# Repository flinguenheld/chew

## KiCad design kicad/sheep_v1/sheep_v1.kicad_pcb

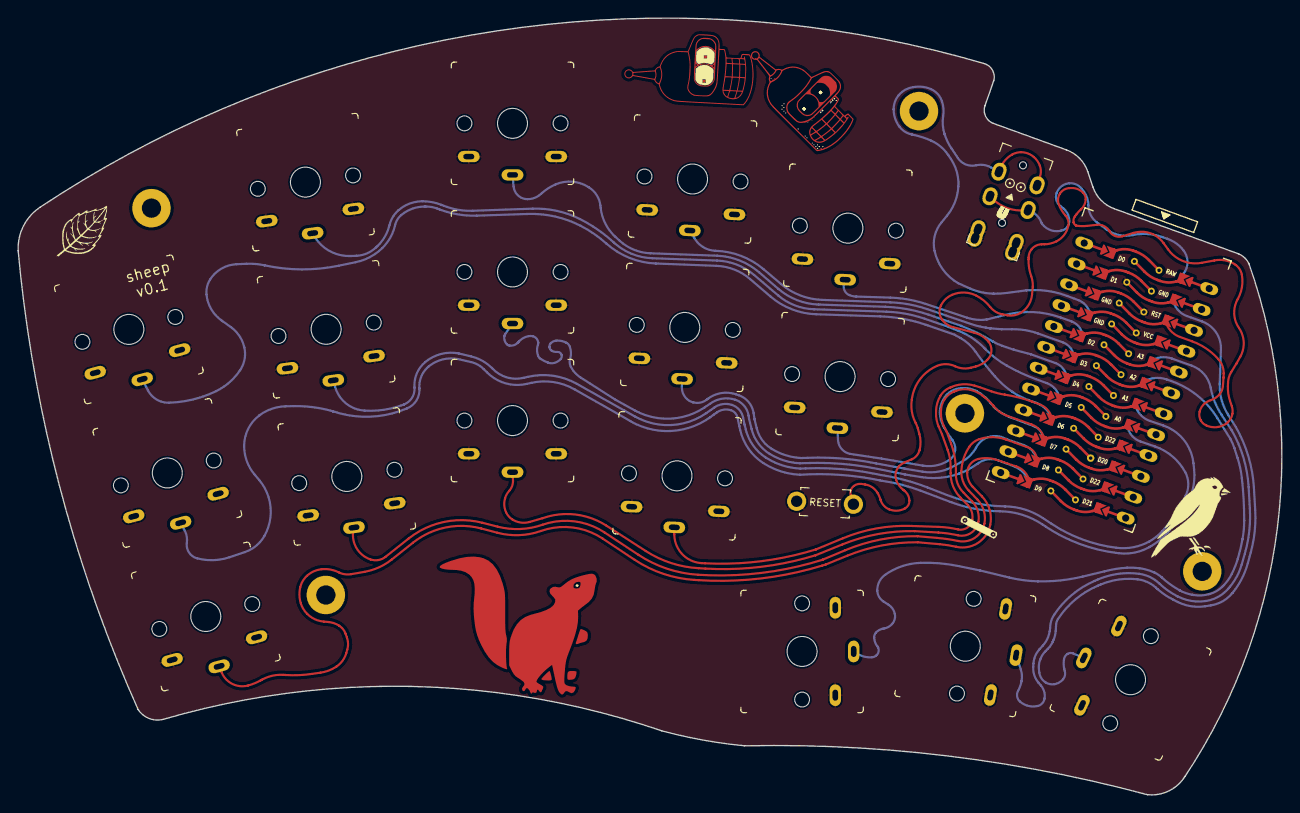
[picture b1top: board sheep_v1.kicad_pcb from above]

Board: 2 copper layers, 144.6 x 88.9 mm, 20 parts (0 on the bottom side), 21 nets.

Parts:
J2: AudioJack4dpb; TRRS-PJ-DPB2
RSW2: SW_PUSH; ResetSW_1side
SW1, SW2, SW3, SW4, SW5, SW6, SW7, SW8, SW9, SW10, SW11, SW12, SW13, SW14, SW15, SW16, SW17: SW_Push; SW_PG1350_rev_DPB
U1: ProMicro-kbd; ProMicro_jumpers_facedown

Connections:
Switch1: SW1.1, U1.20
Switch2: SW2.1, U1.19
Switch3: SW3.1, U1.18
Switch4: SW4.1, U1.17
Switch5: SW5.1, U1.16
Switch6: SW6.1, U1.15
Switch7: SW7.1, U1.14
Switch8: SW8.1, U1.13
Switch9: SW9.1, U1.8
Switch10: SW10.1, U1.7
Switch11: SW11.1, U1.9
Switch12: SW12.1, U1.10
Switch13: SW13.1, U1.11
Switch14: SW14.1, U1.12
Switch15: SW15.1, U1.2
Switch16: SW16.1, U1.5
Switch17: SW17.1, U1.6
Switch18: J2.R1, U1.1
gnd: J2.S, J2.T, RSW2.2, SW1.2, SW2.2, SW3.2, SW4.2, SW5.2, SW6.2, SW7.2, SW8.2, SW9.2, SW10.2, SW11.2, SW12.2, SW13.2, SW14.2, SW15.2, SW16.2, SW17.2, U1.3, U1.4, U1.23
reset: RSW2.1, U1.22
vcc: J2.R2, U1.21
